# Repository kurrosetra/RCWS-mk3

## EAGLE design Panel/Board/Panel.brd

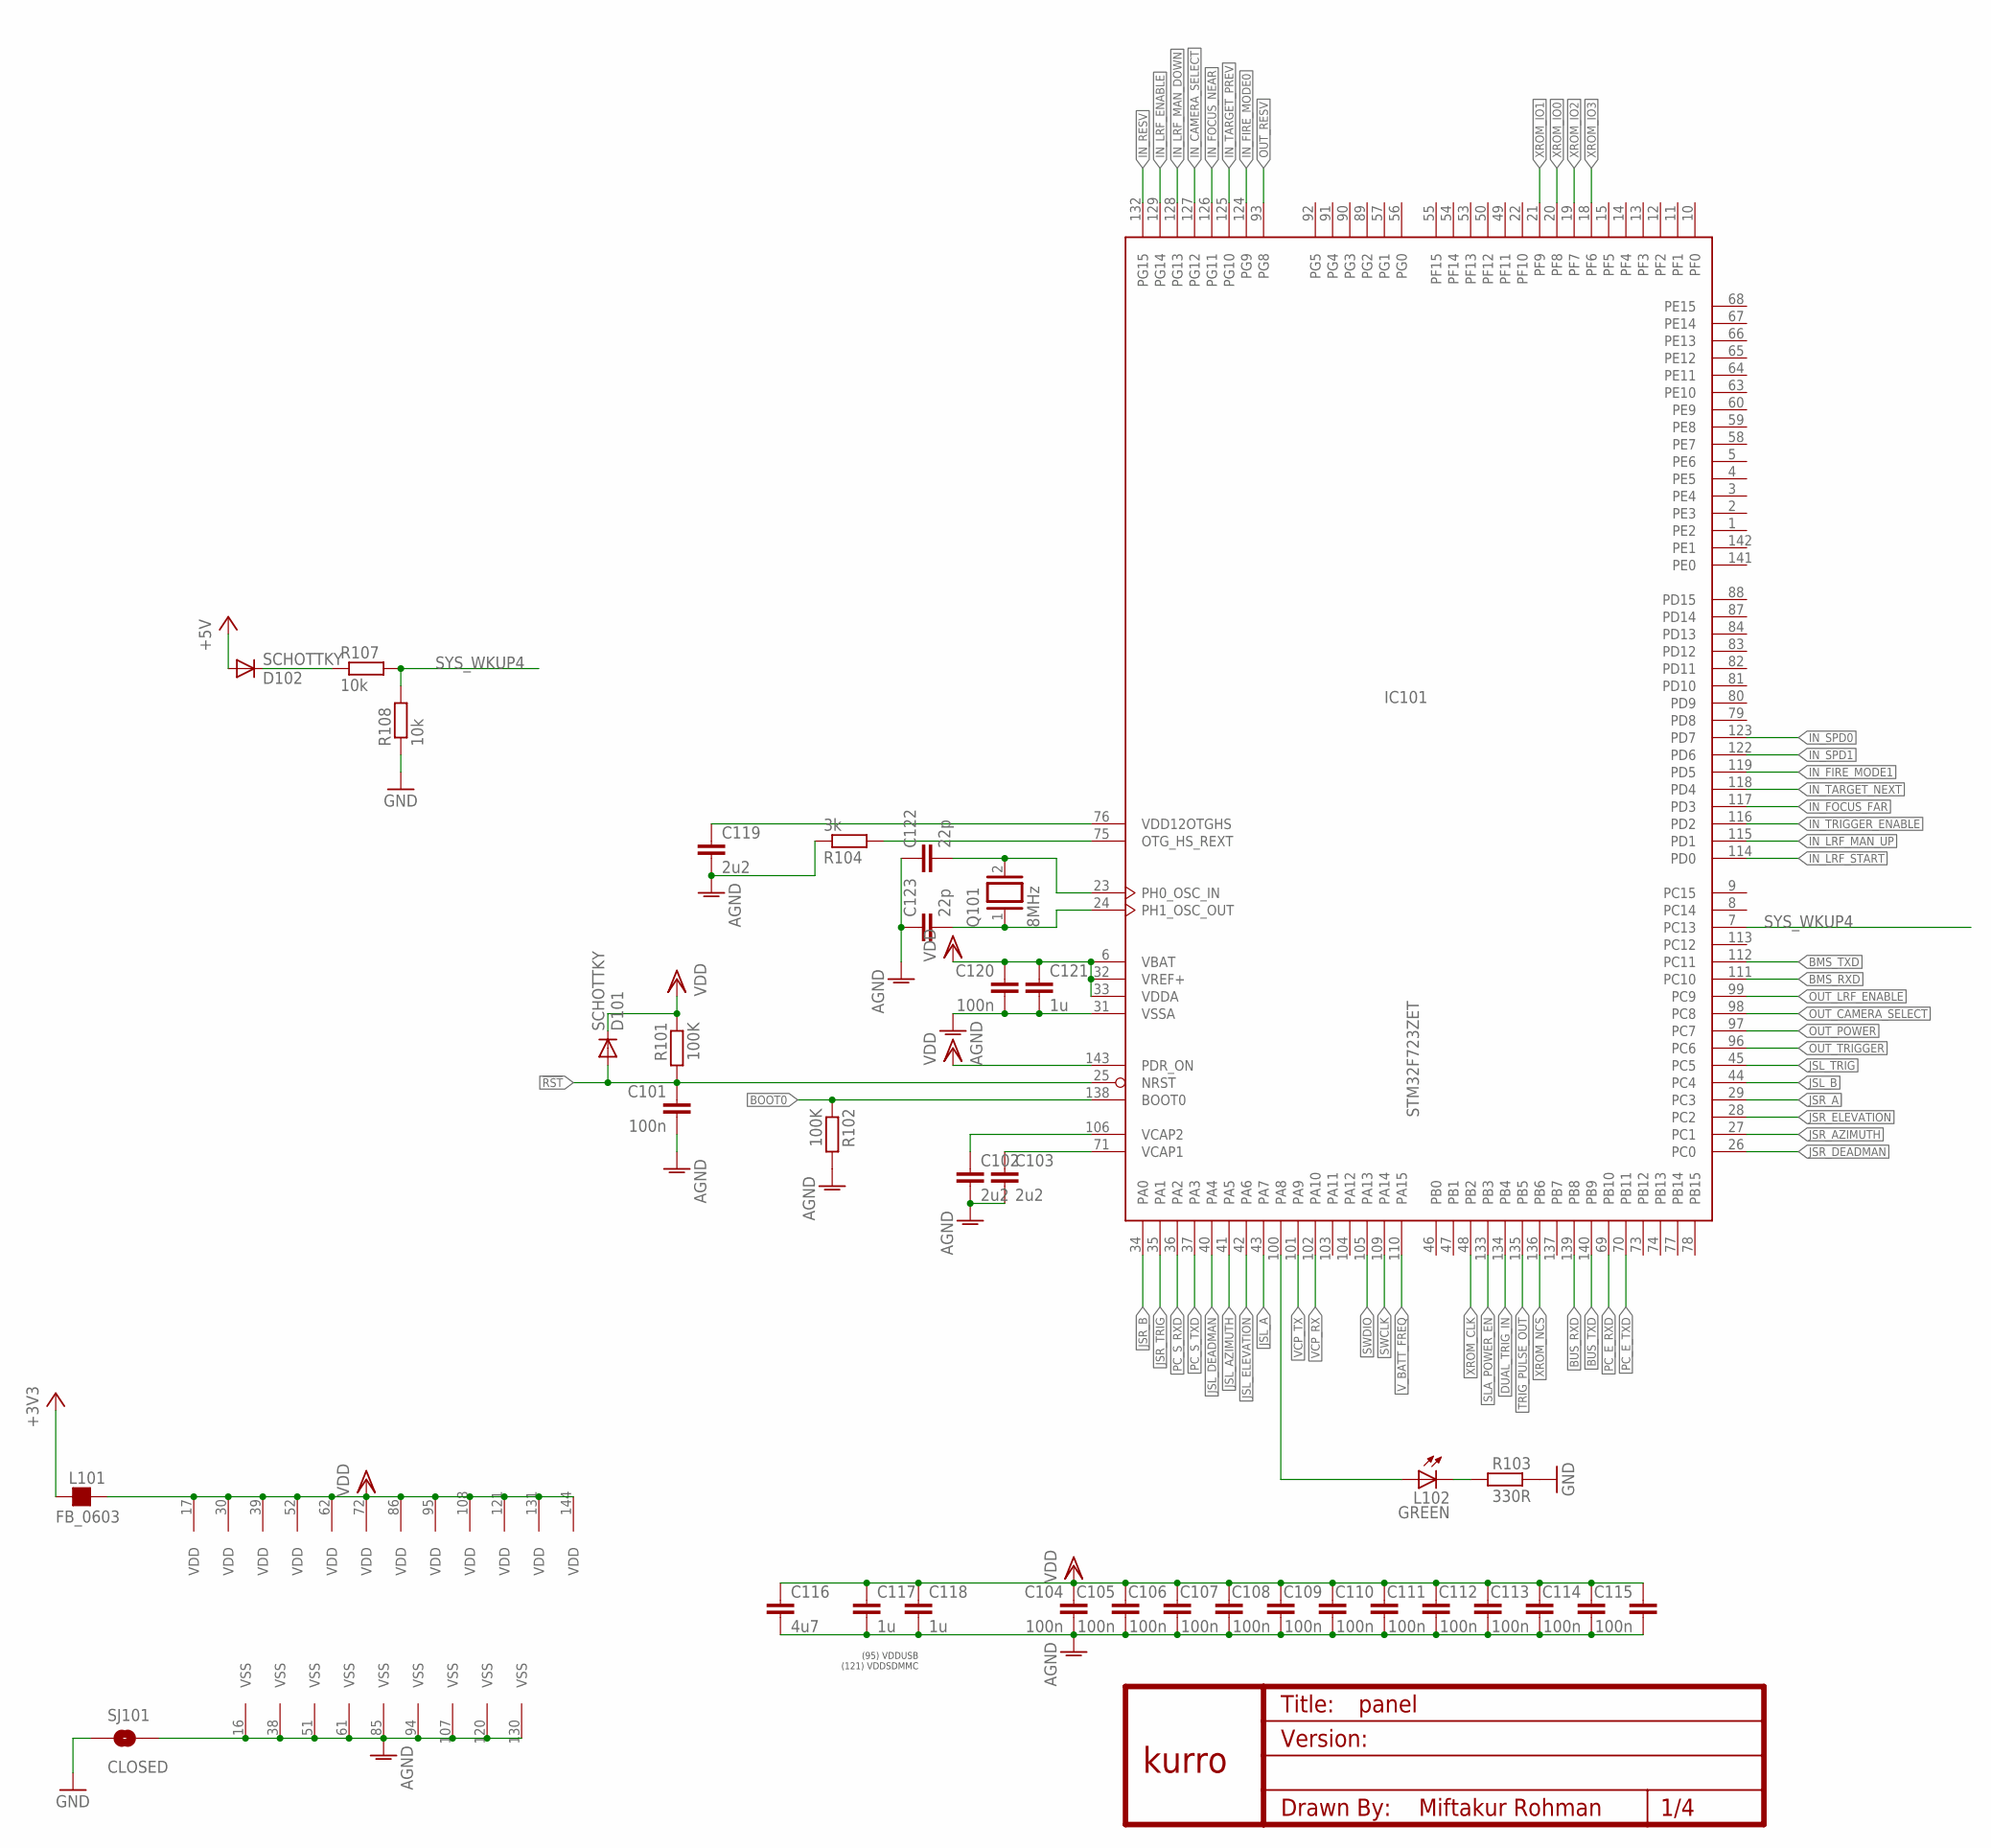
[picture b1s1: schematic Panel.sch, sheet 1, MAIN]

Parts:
C101, C104, C105, C106, C107, C108, C109, C110, C111, C112, C113, C114, C115, C120: 100n; C0603
C102, C103, C119: 2u2; C0805
C116: 4u7; C0805
C117, C118, C121: 1u; C0805
C122, C123: 22p; C0603
D101, D102: SCHOTTKY; MICROMELF-W
IC101: STM32F723ZET; LQFP144-2
L101: FB_0603; L0603
L102: GREEN; CHIP-LED0805
Q101: 8MHz; QS
R101, R102: 100K; R0603
R103: 330R; R0603
R104: 3k; R0603
R107, R108: 10k; R0603
SJ101: CLOSED; SJ_2S-TRACE_THICK
U$2: KURRO_FOOTPRINT; KURRO-LOGO

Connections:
!RST: C101.1, D101.A, IC101.25 (NRST), R101.2; also elsewhere on the board
+3V3: L101.1; also elsewhere on the board
+5V: D102.A; also elsewhere on the board
AGND: C101.2, C102.2, C103.2, C104.2, C105.2, C106.2, C107.2, C108.2, C109.2, C110.2, C111.2, C112.2, C113.2, C114.2, C115.2, C116.2, C117.2, C118.2, C119.2, C120.2, C121.2, C122.1, C123.1, IC101.16 (VSS), IC101.31 (VSSA), IC101.38 (VSS), IC101.51 (VSS), IC101.61 (VSS), IC101.85 (VSS), IC101.94 (VSS), IC101.107 (VSS), IC101.120 (VSS), IC101.130 (VSS), R102.2, R104.1, SJ101.2
BMS_RXD: IC101.111 (PC10); also elsewhere on the board
BMS_TXD: IC101.112 (PC11); also elsewhere on the board
BOOT0: IC101.138 (BOOT0), R102.1; also elsewhere on the board
BUS_RXD: IC101.139 (PB8); also elsewhere on the board
BUS_TXD: IC101.140 (PB9); also elsewhere on the board
DUAL_TRIG_IN: IC101.134 (PB4); also elsewhere on the board
GND: R103.1, R108.1, SJ101.1; also elsewhere on the board
IN_CAMERA_SELECT: IC101.127 (PG12); also elsewhere on the board
IN_FIRE_MODE0: IC101.124 (PG9); also elsewhere on the board
IN_FIRE_MODE1: IC101.119 (PD5); also elsewhere on the board
IN_FOCUS_FAR: IC101.117 (PD3); also elsewhere on the board
IN_FOCUS_NEAR: IC101.126 (PG11); also elsewhere on the board
IN_LRF_ENABLE: IC101.129 (PG14); also elsewhere on the board
IN_LRF_MAN_DOWN: IC101.128 (PG13); also elsewhere on the board
IN_LRF_MAN_UP: IC101.115 (PD1); also elsewhere on the board
IN_LRF_START: IC101.114 (PD0); also elsewhere on the board
IN_RESV: IC101.132 (PG15); also elsewhere on the board
IN_SPD0: IC101.123 (PD7); also elsewhere on the board
IN_SPD1: IC101.122 (PD6); also elsewhere on the board
IN_TARGET_NEXT: IC101.118 (PD4); also elsewhere on the board
IN_TARGET_PREV: IC101.125 (PG10); also elsewhere on the board
IN_TRIGGER_ENABLE: IC101.116 (PD2); also elsewhere on the board
JSL_A: IC101.43 (PA7); also elsewhere on the board
JSL_AZIMUTH: IC101.41 (PA5); also elsewhere on the board
JSL_B: IC101.44 (PC4); also elsewhere on the board
JSL_DEADMAN: IC101.40 (PA4); also elsewhere on the board
JSL_ELEVATION: IC101.42 (PA6); also elsewhere on the board
JSL_TRIG: IC101.45 (PC5); also elsewhere on the board
JSR_A: IC101.29 (PC3); also elsewhere on the board
JSR_AZIMUTH: IC101.27 (PC1); also elsewhere on the board
JSR_B: IC101.34 (PA0); also elsewhere on the board
JSR_DEADMAN: IC101.26 (PC0); also elsewhere on the board
JSR_ELEVATION: IC101.28 (PC2); also elsewhere on the board
JSR_TRIG: IC101.35 (PA1); also elsewhere on the board
unnamed: IC101.75 (OTG_HS_REXT), R104.2
unnamed: L102.C, R103.2
unnamed: IC101.100 (PA8), L102.A
unnamed: C119.1, IC101.76 (VDD12OTGHS)
unnamed: C123.2, IC101.24 (PH1_OSC_OUT), Q101.1
unnamed: C122.2, IC101.23 (PH0_OSC_IN), Q101.2
unnamed: D102.C, R107.1
OUT_CAMERA_SELECT: IC101.98 (PC8); also elsewhere on the board
OUT_LRF_ENABLE: IC101.99 (PC9); also elsewhere on the board
OUT_POWER: IC101.97 (PC7); also elsewhere on the board
OUT_RESV: IC101.93 (PG8); also elsewhere on the board
OUT_TRIGGER: IC101.96 (PC6); also elsewhere on the board
PC_E_RXD: IC101.69 (PB10); also elsewhere on the board
PC_E_TXD: IC101.70 (PB11); also elsewhere on the board
PC_S_RXD: IC101.36 (PA2); also elsewhere on the board
PC_S_TXD: IC101.37 (PA3); also elsewhere on the board
SLA_POWER_EN: IC101.133 (PB3); also elsewhere on the board
SWCLK: IC101.109 (PA14); also elsewhere on the board
SWDIO: IC101.105 (PA13); also elsewhere on the board
SYS_WKUP4: IC101.7 (PC13), R107.2, R108.2
TRIG_PULSE_OUT: IC101.135 (PB5); also elsewhere on the board
VCAP1: C103.1, IC101.71 (VCAP1)
VCAP2: C102.1, IC101.106 (VCAP2)
VCP_RX: IC101.102 (PA10); also elsewhere on the board
VCP_TX: IC101.101 (PA9); also elsewhere on the board
VDD: C104.1, C105.1, C106.1, C107.1, C108.1, C109.1, C110.1, C111.1, C112.1, C113.1, C114.1, C115.1, C116.1, C117.1, C118.1, C120.1, C121.1, D101.C, IC101.6 (VBAT), IC101.17 (VDD), IC101.30 (VDD), IC101.32 (VREF+), IC101.33 (VDDA), IC101.39 (VDD), IC101.52 (VDD), IC101.62 (VDD), IC101.72 (VDD), IC101.86 (VDD), IC101.95 (VDD), IC101.108 (VDD), IC101.121 (VDD), IC101.131 (VDD), IC101.143 (PDR_ON), IC101.144 (VDD), L101.2, R101.1; also elsewhere on the board
V_BATT_FREQ: IC101.110 (PA15); also elsewhere on the board
XROM_CLK: IC101.48 (PB2); also elsewhere on the board
XROM_IO0: IC101.20 (PF8); also elsewhere on the board
XROM_IO1: IC101.21 (PF9); also elsewhere on the board
XROM_IO2: IC101.19 (PF7); also elsewhere on the board
XROM_IO3: IC101.18 (PF6); also elsewhere on the board
XROM_NCS: IC101.136 (PB6); also elsewhere on the board

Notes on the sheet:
(95) VDDUSB (121) VDDSDMMC

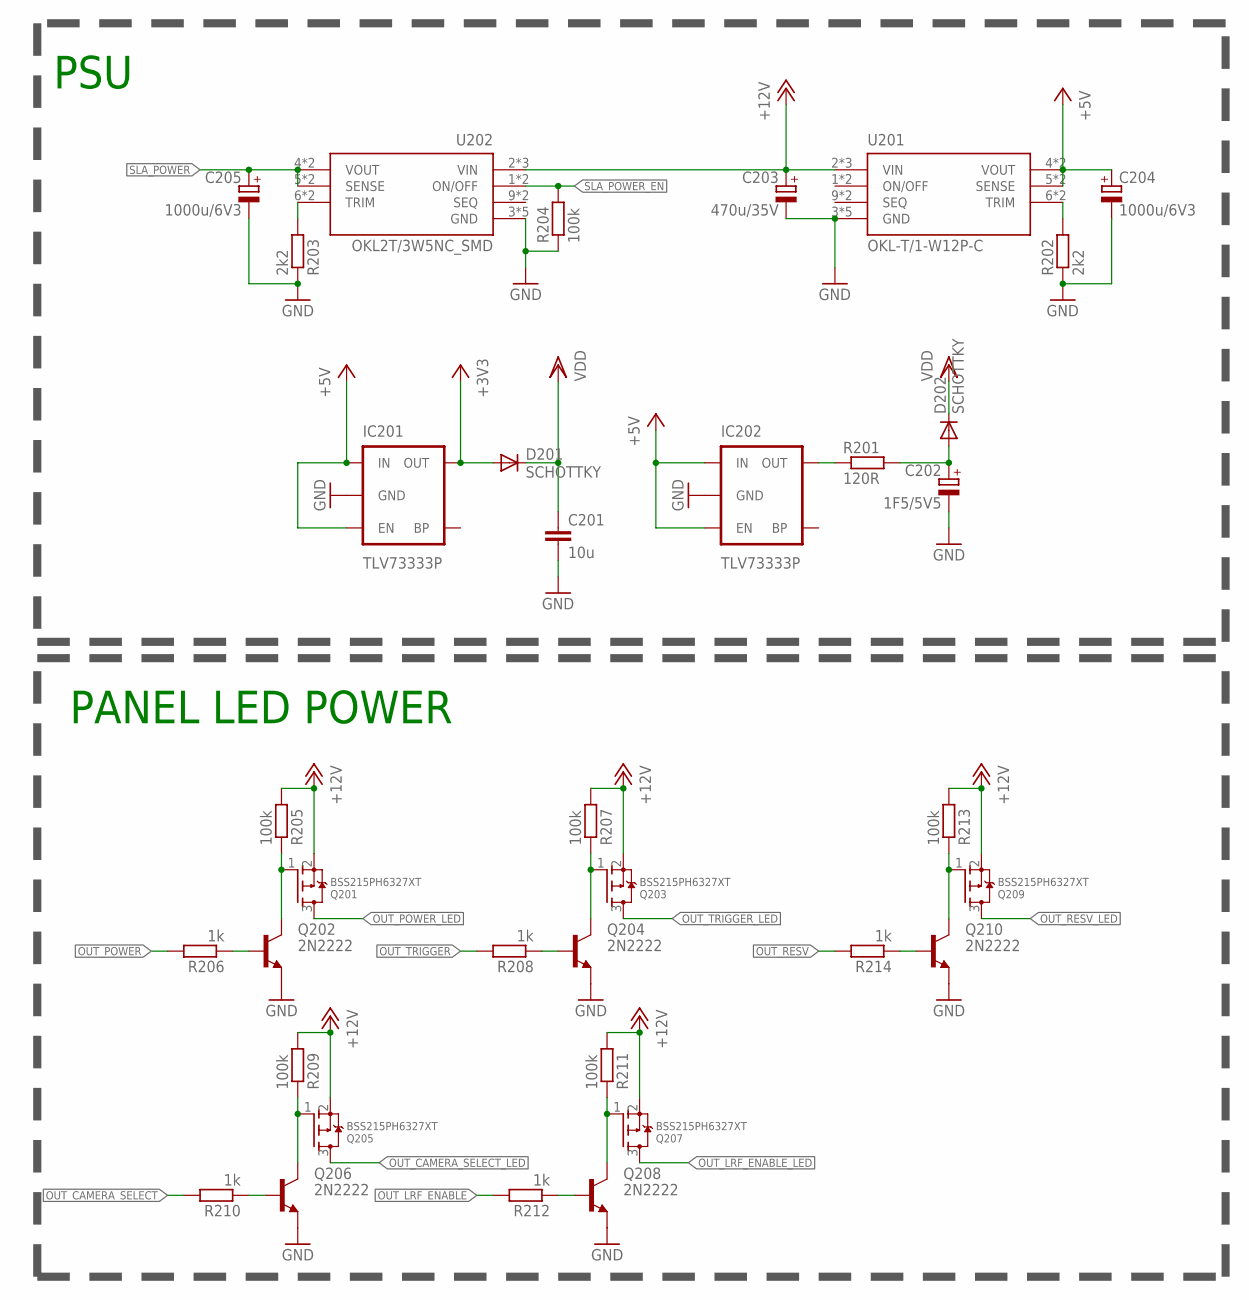
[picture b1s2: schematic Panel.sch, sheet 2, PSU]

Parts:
C201: 10u; C0805
C202: 1F5/5V5; SC_1F/5V5
C203: 470u/35V; 153CLV-1012
C204, C205: 1000u/6V3; 153CLV-0810
D201, D202: SCHOTTKY; MICROMELF-W
IC201, IC202: TLV73333P; SOT23-5
Q201, Q203, Q205, Q207, Q209: BSS215PH6327XT; SOT23-W
Q202, Q204, Q206, Q208, Q210: 2N2222; SOT23
R201: 120R; R0603
R202, R203: 2k2; R0603
R204, R205, R207, R209, R211, R213: 100k; R0603
R206, R208, R210, R212, R214: 1k; R0603
U201: OKL-T/1-W12P-C; OKL2T/3W5NC
U202: OKL2T/3W5NC_SMD; OKL2T/3W5NC

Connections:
+3V3: D201.A, IC201.5 (OUT); also elsewhere on the board
+5V: C204.+, IC201.1 (IN), IC201.3 (EN), IC202.1 (IN), IC202.3 (EN), U201.4 (VOUT), U201.4@1 (VOUT), U201.5 (SENSE), U201.5@1 (SENSE); also elsewhere on the board
+12V: C203.+, Q201.2 (S), Q203.2 (S), Q205.2 (S), Q207.2 (S), Q209.2 (S), R205.2, R207.2, R209.2, R211.2, R213.2, U201.2 (VIN), U201.2@1 (VIN), U201.2@2 (VIN), U202.2 (VIN), U202.2@1 (VIN), U202.2@2 (VIN); also elsewhere on the board
GND: C201.2, C202.2 (-), C203.-, C204.-, C205.-, IC201.2 (GND), IC202.2 (GND), Q202.2 (E), Q204.2 (E), Q206.2 (E), Q208.2 (E), Q210.2 (E), R202.1, R203.1, R204.1, U201.3 (GND), U201.3@1 (GND), U201.3@2 (GND), U201.7 (GND), U201.7@1 (GND), U202.3 (GND), U202.3@1 (GND), U202.3@2 (GND), U202.7 (GND), U202.7@1 (GND); also elsewhere on the board
unnamed: R202.2, U201.6 (TRIM), U201.6@1 (TRIM)
unnamed: IC202.5 (OUT), R201.1
unnamed: Q209.1 (G), Q210.3 (C), R213.1
unnamed: Q201.1 (G), Q202.3 (C), R205.1
unnamed: Q202.1 (B), R206.1
unnamed: Q203.1 (G), Q204.3 (C), R207.1
unnamed: Q204.1 (B), R208.1
unnamed: Q210.1 (B), R214.1
unnamed: Q205.1 (G), Q206.3 (C), R209.1
unnamed: Q206.1 (B), R210.1
unnamed: Q207.1 (G), Q208.3 (C), R211.1
unnamed: Q208.1 (B), R212.1
unnamed: R203.2, U202.6 (TRIM), U202.6@1 (TRIM)
OUT_CAMERA_SELECT: R210.2; also elsewhere on the board
OUT_CAMERA_SELECT_LED: Q205.3 (D); also elsewhere on the board
OUT_LRF_ENABLE: R212.2; also elsewhere on the board
OUT_LRF_ENABLE_LED: Q207.3 (D); also elsewhere on the board
OUT_POWER: R206.2; also elsewhere on the board
OUT_POWER_LED: Q201.3 (D); also elsewhere on the board
OUT_RESV: R214.2; also elsewhere on the board
OUT_RESV_LED: Q209.3 (D); also elsewhere on the board
OUT_TRIGGER: R208.2; also elsewhere on the board
OUT_TRIGGER_LED: Q203.3 (D); also elsewhere on the board
SLA_POWER: C205.+, U202.4 (VOUT), U202.4@1 (VOUT), U202.5 (SENSE), U202.5@1 (SENSE); also elsewhere on the board
SLA_POWER_EN: R204.2, U202.1 (ON/OFF), U202.1@1 (ON/OFF); also elsewhere on the board
VDD: C201.1, D201.C, D202.C; also elsewhere on the board
V_SCAP1: C202.1 (+), D202.A, R201.2

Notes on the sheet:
PSU
PANEL LED POWER

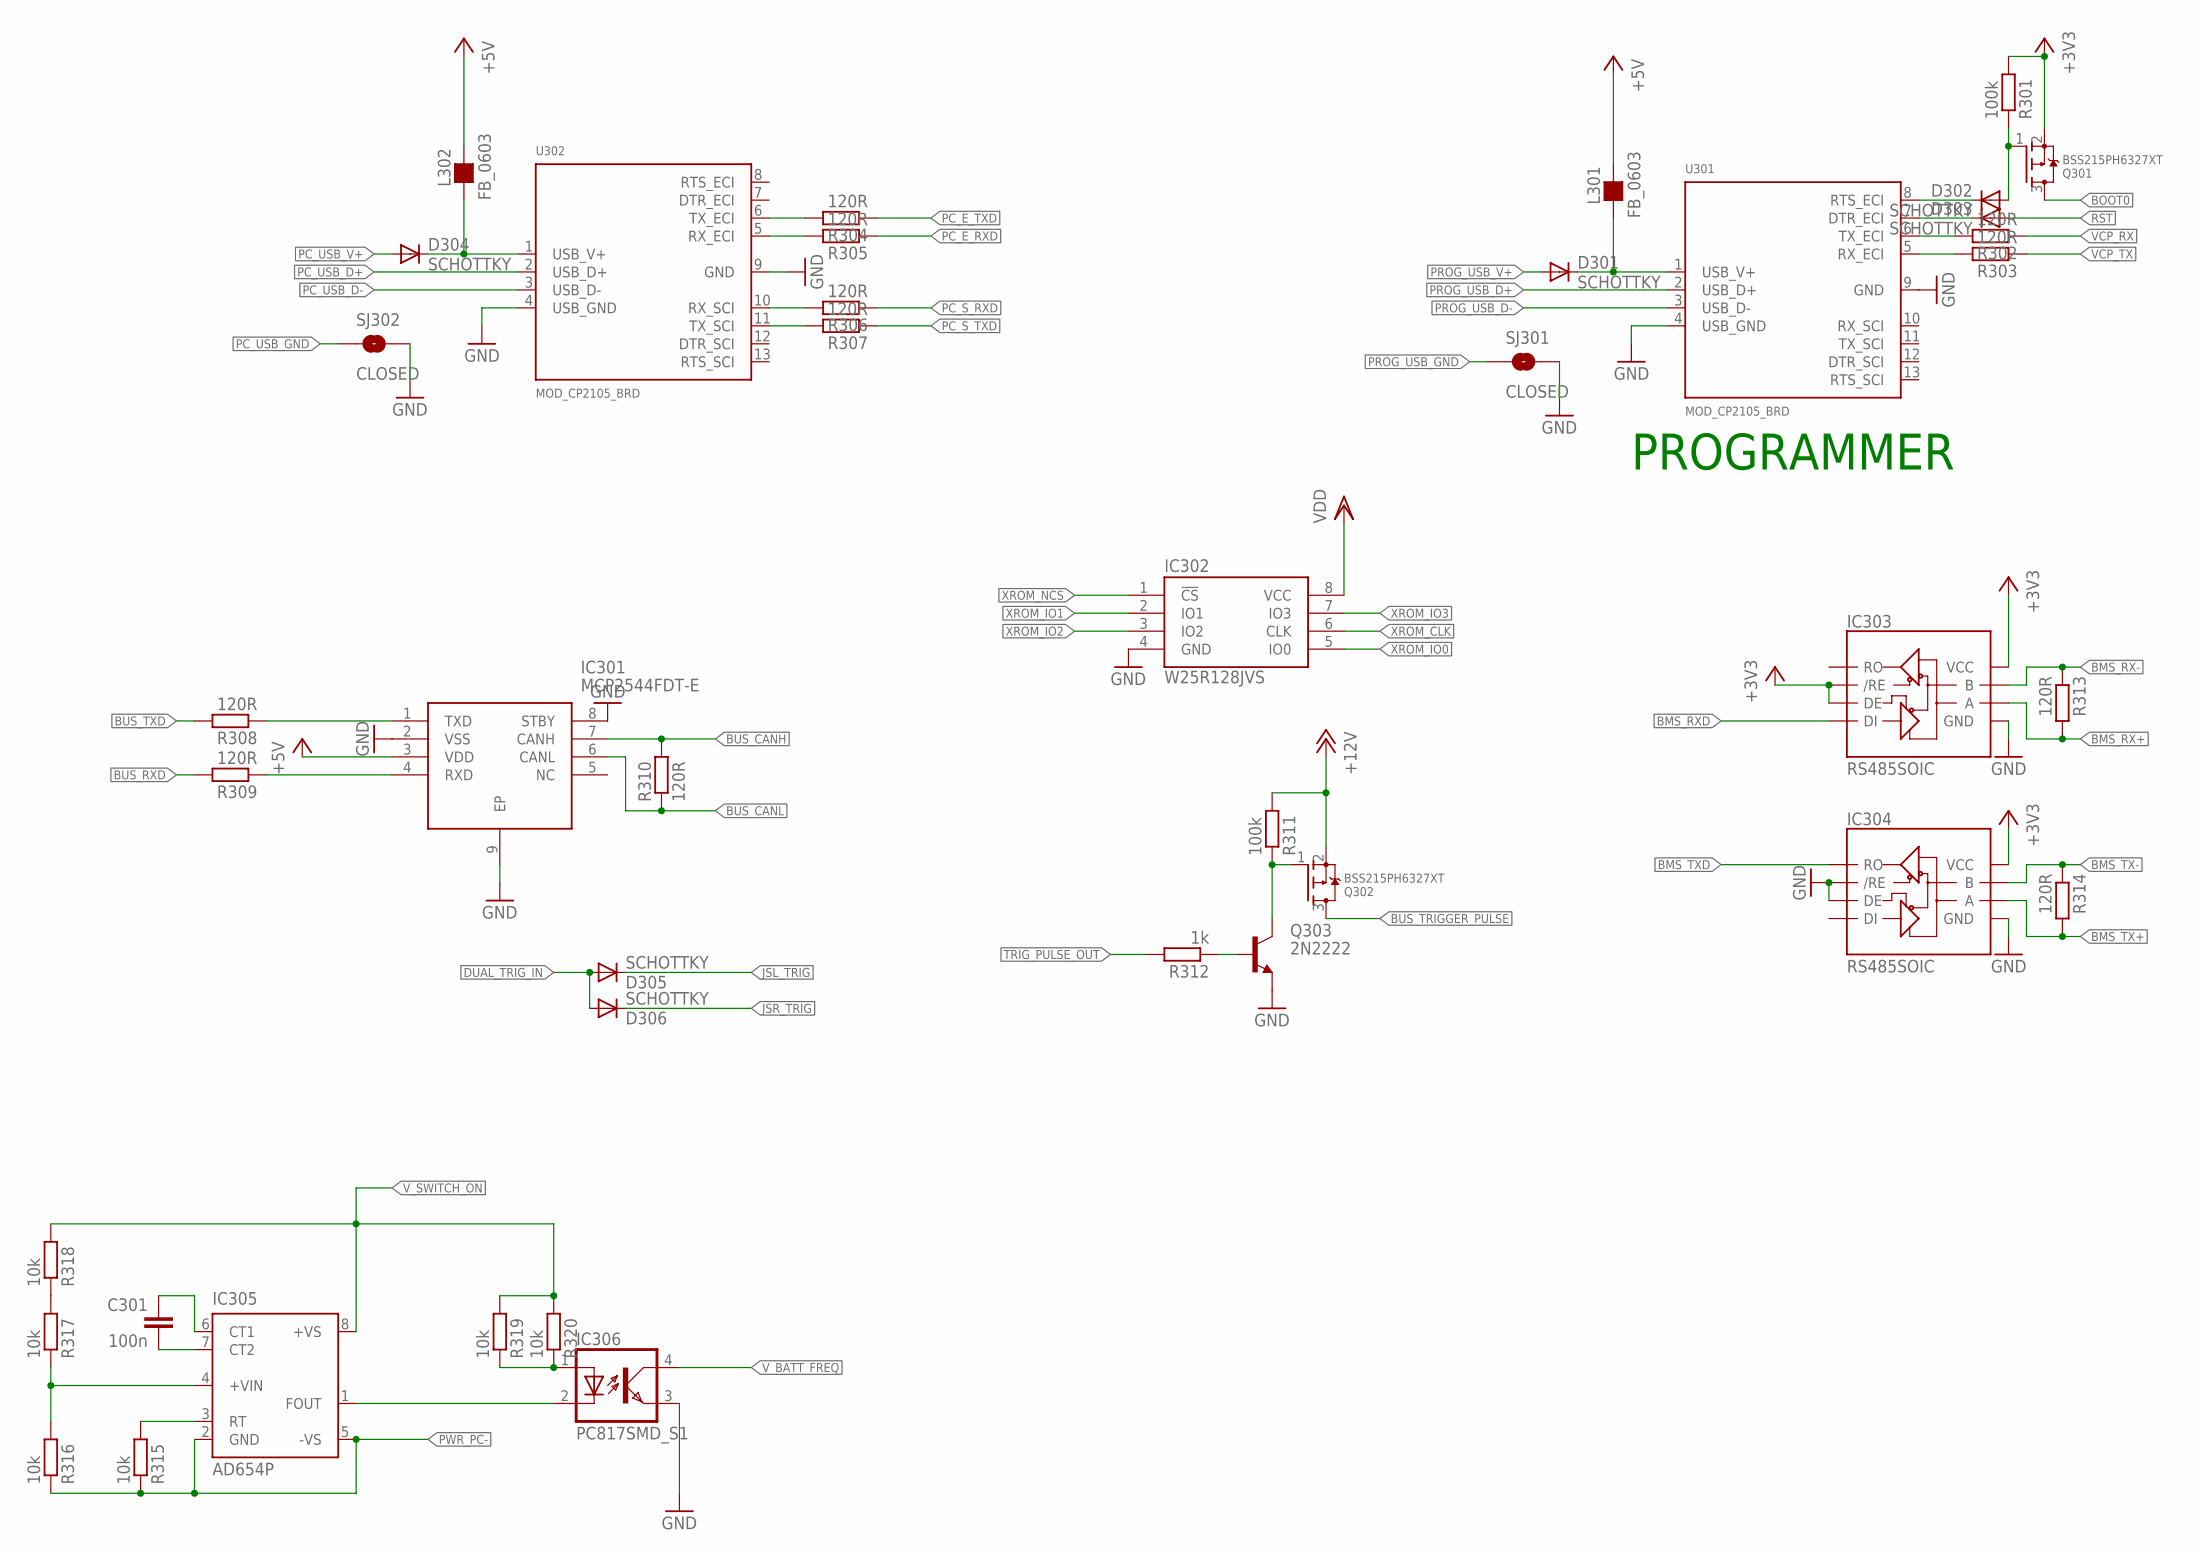
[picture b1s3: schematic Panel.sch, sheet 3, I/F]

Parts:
C301: 100n; C0603
D301, D302, D303, D304, D305, D306: SCHOTTKY; MICROMELF-W
IC301: MCP2544FDT-E; TDFN-8
IC302: W25R128JVS; SO08
IC303, IC304: RS485SOIC; SO08
IC305: AD654P; DIL08
IC306: PC817SMD_S1; PC817SMD
L301, L302: FB_0603; L0603
Q301, Q302: BSS215PH6327XT; SOT23-W
Q303: 2N2222; SOT23
R301, R311: 100k; R0603
R302, R303, R304, R305, R306, R307, R308, R309, R310, R313, R314: 120R; R0603
R312: 1k; R0603
R315, R316, R317, R318, R319, R320: 10k; R0603
SJ301, SJ302: CLOSED; SJ_2S-TRACE_THICK
U301, U302: MOD_CP2105_BRD; MOD_CP2105_BOARD

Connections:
!RST: D303.A; also elsewhere on the board
+3V3: IC303.2 (/RE), IC303.3 (DE), IC303.8 (VCC), IC304.8 (VCC), Q301.2 (S), R301.2; also elsewhere on the board
+5V: IC301.3 (VDD), L301.2, L302.2; also elsewhere on the board
+12V: Q302.2 (S), R311.2; also elsewhere on the board
BMS_RX+: IC303.6 (A), R313.2; also elsewhere on the board
BMS_RX-: IC303.7 (B), R313.1; also elsewhere on the board
BMS_RXD: IC303.4 (DI); also elsewhere on the board
BMS_TX+: IC304.6 (A), R314.2; also elsewhere on the board
BMS_TX-: IC304.7 (B), R314.1; also elsewhere on the board
BMS_TXD: IC304.1 (RO); also elsewhere on the board
BOOT0: Q301.3 (D); also elsewhere on the board
BUS_CANH: IC301.7 (CANH), R310.2; also elsewhere on the board
BUS_CANL: IC301.6 (CANL), R310.1; also elsewhere on the board
BUS_RXD: R309.2; also elsewhere on the board
BUS_TRIGGER_PULSE: Q302.3 (D); also elsewhere on the board
BUS_TXD: R308.2; also elsewhere on the board
DUAL_TRIG_IN: D305.A, D306.A; also elsewhere on the board
GND: IC301.2 (VSS), IC301.8 (STBY), IC301.9 (EP), IC302.4 (GND), IC303.5 (GND), IC304.2 (/RE), IC304.3 (DE), IC304.5 (GND), IC306.3 (EMIT), Q303.2 (E), SJ301.2, SJ302.2, U301.4 (USB_GND), U301.9 (GND), U302.4 (USB_GND), U302.9 (GND); also elsewhere on the board
JSL_TRIG: D305.C; also elsewhere on the board
JSR_TRIG: D306.C; also elsewhere on the board
unnamed: Q302.1 (G), Q303.3 (C), R311.1
unnamed: Q303.1 (B), R312.1
unnamed: IC301.1 (TXD), R308.1
unnamed: IC301.4 (RXD), R309.1
unnamed: R303.2, U301.5 (RX_ECI)
unnamed: IC305.1 (FOUT), IC306.2 (C)
unnamed: R302.2, U301.6 (TX_ECI)
unnamed: D303.C, U301.7 (DTR_ECI)
unnamed: D302.C, U301.8 (RTS_ECI)
unnamed: D301.C, L301.1, U301.1 (USB_V+)
unnamed: D302.A, Q301.1 (G), R301.1
unnamed: R305.2, U302.5 (RX_ECI)
unnamed: R304.2, U302.6 (TX_ECI)
unnamed: R306.2, U302.10 (RX_SCI)
unnamed: R307.2, U302.11 (TX_SCI)
unnamed: IC306.1 (A), R319.1, R320.1
unnamed: D304.C, L302.1, U302.1 (USB_V+)
unnamed: IC305.3 (RT), R315.2
unnamed: C301.2, IC305.7 (CT2)
unnamed: C301.1, IC305.6 (CT1)
unnamed: IC305.4 (+VIN), R316.2, R317.1
unnamed: R317.2, R318.1
PC_E_RXD: R305.1; also elsewhere on the board
PC_E_TXD: R304.1; also elsewhere on the board
PC_S_RXD: R306.1; also elsewhere on the board
PC_S_TXD: R307.1; also elsewhere on the board
PC_USB_D+: U302.2 (USB_D+); also elsewhere on the board
PC_USB_D-: U302.3 (USB_D-); also elsewhere on the board
PC_USB_GND: SJ302.1; also elsewhere on the board
PC_USB_V+: D304.A; also elsewhere on the board
PROG_USB_D+: U301.2 (USB_D+); also elsewhere on the board
PROG_USB_D-: U301.3 (USB_D-); also elsewhere on the board
PROG_USB_GND: SJ301.1; also elsewhere on the board
PROG_USB_V+: D301.A; also elsewhere on the board
PWR_PC-: IC305.2 (GND), IC305.5 (-VS), R315.1, R316.1; also elsewhere on the board
TRIG_PULSE_OUT: R312.2; also elsewhere on the board
VCP_RX: R302.1; also elsewhere on the board
VCP_TX: R303.1; also elsewhere on the board
VDD: IC302.8 (VCC); also elsewhere on the board
V_BATT_FREQ: IC306.4 (COL); also elsewhere on the board
V_SWITCH_ON: IC305.8 (+VS), R318.2, R319.2, R320.2; also elsewhere on the board
XROM_CLK: IC302.6 (CLK); also elsewhere on the board
XROM_IO0: IC302.5 (IO0); also elsewhere on the board
XROM_IO1: IC302.2 (IO1); also elsewhere on the board
XROM_IO2: IC302.3 (IO2); also elsewhere on the board
XROM_IO3: IC302.7 (IO3); also elsewhere on the board
XROM_NCS: IC302.1 (!CS); also elsewhere on the board

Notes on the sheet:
PROGRAMMER

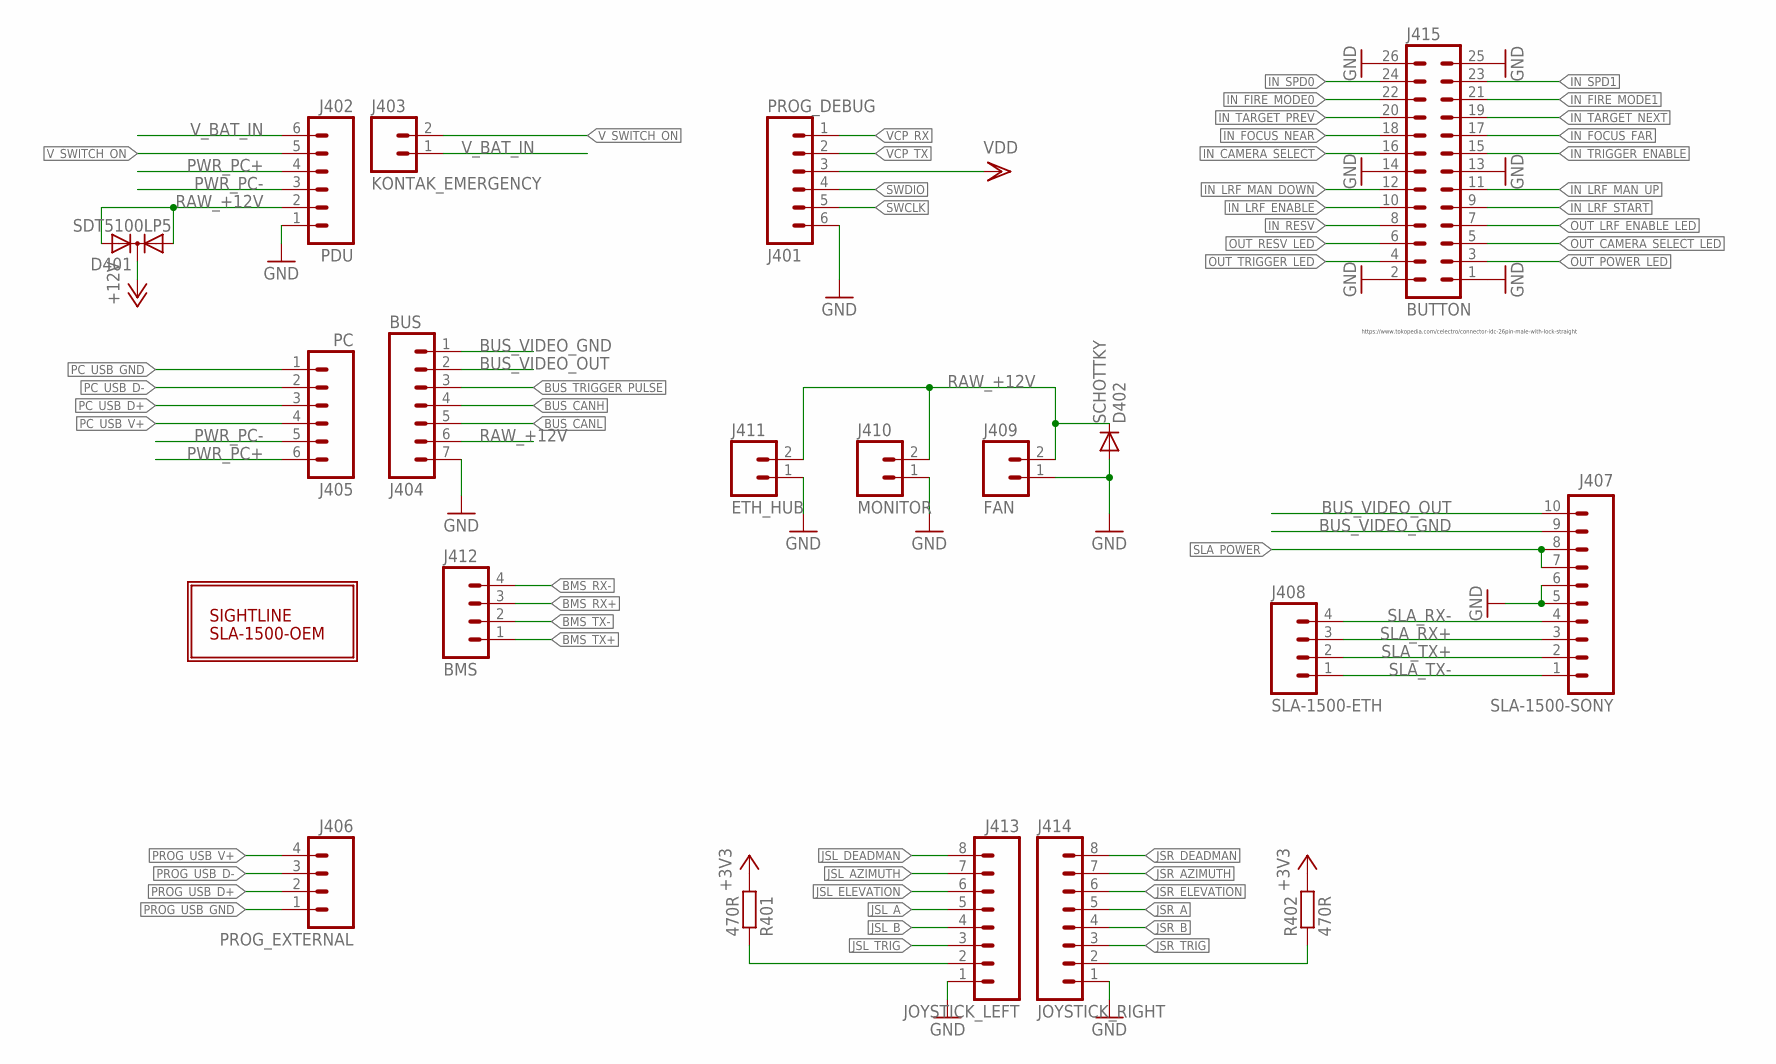
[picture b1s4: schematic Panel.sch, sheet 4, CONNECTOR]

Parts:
D401: SDT5100LP5; POWERDI5-3
D402: SCHOTTKY; MICROMELF-W
J401: PROG_DEBUG; XHS-6-VERT-SMD
J402: PDU; XHS-6-RA
J403: KONTAK_EMERGENCY; XHS-2-RA
J404: BUS; XHS-7-RA
J405: PC; XHS-6-RA
J406: PROG_EXTERNAL; XHS-4-RA
J407: SLA-1500-SONY; XHS-10-VERT
J408: SLA-1500-ETH; XHS-4-RA
J409: FAN; XHS-2-VERT
J410: MONITOR; XHS-2-RA
J411: ETH_HUB; XHS-2-VERT
J412: BMS; XHS-4-RA
J413: JOYSTICK_LEFT; XHS-8-RA
J414: JOYSTICK_RIGHT; XHS-8-RA
J415: BUTTON; 26V
R401, R402: 470R; R0603
U401: SLA-1500-OEM
U402: SLA-1500-OEM-RESTRICT; SLA_1500-OEM-RESTRICT

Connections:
+3V3: R401.2, R402.2; also elsewhere on the board
+12V: D401.3; also elsewhere on the board
BMS_RX+: J412.3; also elsewhere on the board
BMS_RX-: J412.4; also elsewhere on the board
BMS_TX+: J412.1; also elsewhere on the board
BMS_TX-: J412.2; also elsewhere on the board
BUS_CANH: J404.4; also elsewhere on the board
BUS_CANL: J404.5; also elsewhere on the board
BUS_TRIGGER_PULSE: J404.3; also elsewhere on the board
BUS_VIDEO_GND: J404.1, J407.9
BUS_VIDEO_OUT: J404.2, J407.10
GND: D402.A, J401.6, J402.1, J404.7, J407.5, J407.6, J409.1, J410.1, J411.1, J413.1, J414.1, J415.1, J415.2, J415.13, J415.14, J415.25, J415.26; also elsewhere on the board
IN_CAMERA_SELECT: J415.16; also elsewhere on the board
IN_FIRE_MODE0: J415.22; also elsewhere on the board
IN_FIRE_MODE1: J415.21; also elsewhere on the board
IN_FOCUS_FAR: J415.17; also elsewhere on the board
IN_FOCUS_NEAR: J415.18; also elsewhere on the board
IN_LRF_ENABLE: J415.10; also elsewhere on the board
IN_LRF_MAN_DOWN: J415.12; also elsewhere on the board
IN_LRF_MAN_UP: J415.11; also elsewhere on the board
IN_LRF_START: J415.9; also elsewhere on the board
IN_RESV: J415.8; also elsewhere on the board
IN_SPD0: J415.24; also elsewhere on the board
IN_SPD1: J415.23; also elsewhere on the board
IN_TARGET_NEXT: J415.19; also elsewhere on the board
IN_TARGET_PREV: J415.20; also elsewhere on the board
IN_TRIGGER_ENABLE: J415.15; also elsewhere on the board
JSL_A: J413.5; also elsewhere on the board
JSL_AZIMUTH: J413.7; also elsewhere on the board
JSL_B: J413.4; also elsewhere on the board
JSL_DEADMAN: J413.8; also elsewhere on the board
JSL_ELEVATION: J413.6; also elsewhere on the board
JSL_TRIG: J413.3; also elsewhere on the board
JSR_A: J414.5; also elsewhere on the board
JSR_AZIMUTH: J414.7; also elsewhere on the board
JSR_B: J414.4; also elsewhere on the board
JSR_DEADMAN: J414.8; also elsewhere on the board
JSR_ELEVATION: J414.6; also elsewhere on the board
JSR_TRIG: J414.3; also elsewhere on the board
unnamed: J414.2, R402.1
unnamed: J413.2, R401.1
OUT_CAMERA_SELECT_LED: J415.5; also elsewhere on the board
OUT_LRF_ENABLE_LED: J415.7; also elsewhere on the board
OUT_POWER_LED: J415.3; also elsewhere on the board
OUT_RESV_LED: J415.6; also elsewhere on the board
OUT_TRIGGER_LED: J415.4; also elsewhere on the board
PC_USB_D+: J405.3; also elsewhere on the board
PC_USB_D-: J405.2; also elsewhere on the board
PC_USB_GND: J405.1; also elsewhere on the board
PC_USB_V+: J405.4; also elsewhere on the board
PROG_USB_D+: J406.2; also elsewhere on the board
PROG_USB_D-: J406.3; also elsewhere on the board
PROG_USB_GND: J406.1; also elsewhere on the board
PROG_USB_V+: J406.4; also elsewhere on the board
PWR_PC+: J402.4, J405.6
PWR_PC-: J402.3, J405.5; also elsewhere on the board
RAW_+12V: D401.1, D401.2, D402.C, J402.2, J404.6, J409.2, J410.2, J411.2
SLA_POWER: J407.7, J407.8; also elsewhere on the board
SLA_RX+: J407.3, J408.3
SLA_RX-: J407.4, J408.4
SLA_TX+: J407.2, J408.2
SLA_TX-: J407.1, J408.1
SWCLK: J401.5; also elsewhere on the board
SWDIO: J401.4; also elsewhere on the board
VCP_RX: J401.1; also elsewhere on the board
VCP_TX: J401.2; also elsewhere on the board
VDD: J401.3; also elsewhere on the board
V_BAT_IN: J402.6, J403.1
V_SWITCH_ON: J402.5, J403.2; also elsewhere on the board

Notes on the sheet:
https://www.tokopedia.com/celectro/connector-idc-26pin-male-with-lock-straight

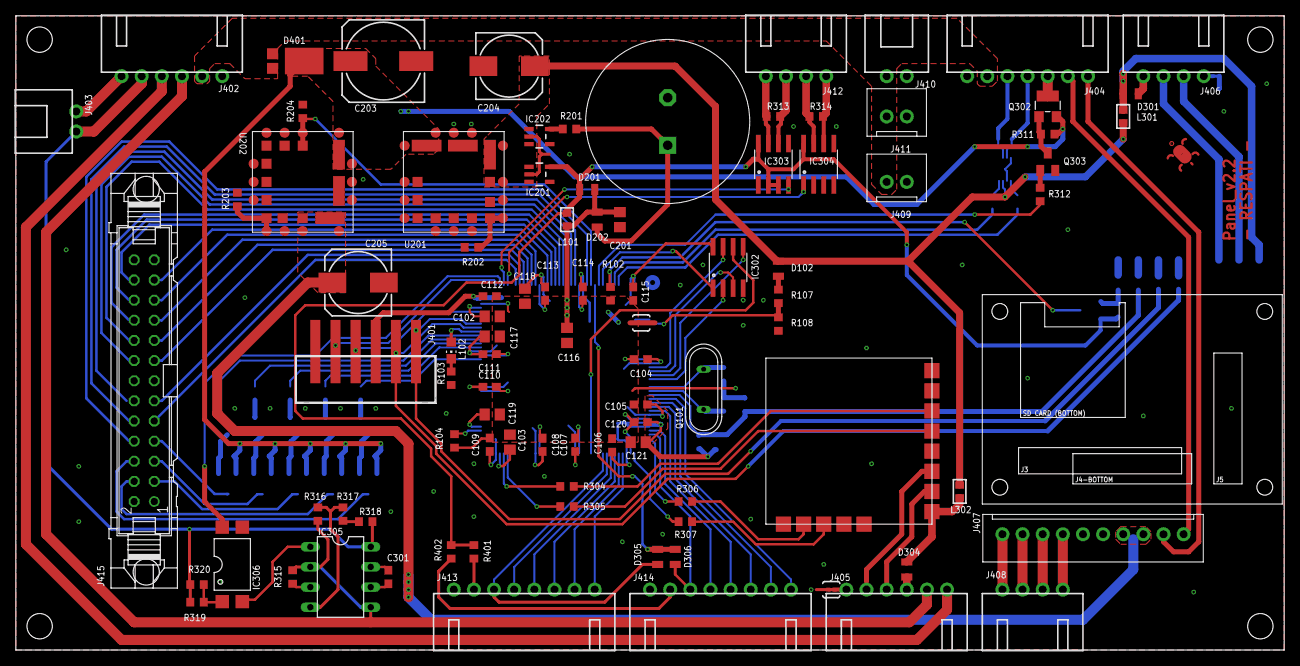
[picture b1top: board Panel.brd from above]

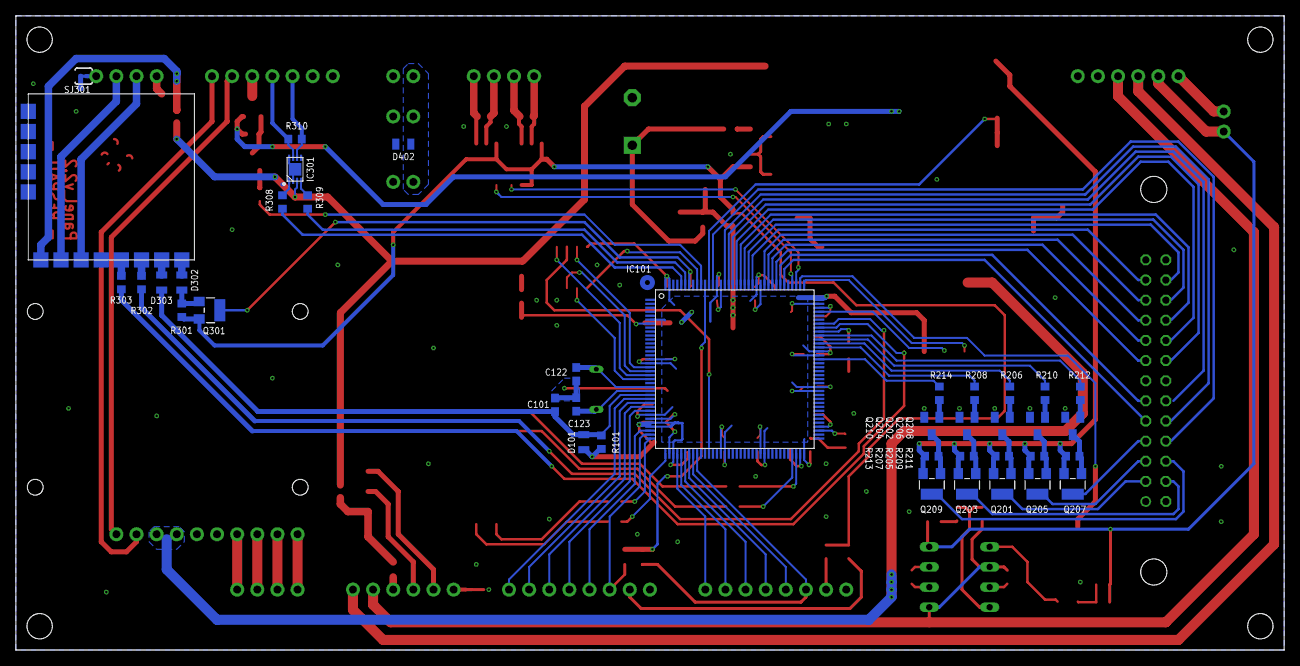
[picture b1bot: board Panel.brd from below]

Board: 2 copper layers, 160.0 x 80.0 mm, 135 parts (40 on the bottom side), 142 nets.

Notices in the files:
parts and their libraries:
SparkFun-Connectors: Licensing: CC v3.0 Share-Alike You are welcome to use this library for commercial purposes.
rc-master: Copyright (C) 2007, Bob Starr
